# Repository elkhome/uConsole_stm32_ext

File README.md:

# uConsole_stm32_ext
STM32 extension card for uConsole.

Design is not finished and has not been tested.

Design based on dotcypress's uHub board, with identical USB port positioning: https://github.com/dotcypress/uhub

STM32 design learned from Sleepdealr's Kingsaver Replacement PCB: https://github.com/Sleepdealr/Kingsaver-Replacement-PCB

The goal is to get some of the functionality of both boards together, at a slightly lower manufacturing cost.

- Two USB C ports connected directly to the USB C pins, to avoid the need for a USB hub.
- STM32 replacing the RP2040, to avoid the need for crystal or flash components.
- Connecting the microcontroller to the uConsole via GPIO instead of USB, to both preserve uConsole’s USB lines and make the microcontroller’s USB lines externally accessible.
- Same USB C ports in the same position as the uHub, so the same faceplate should work for both.

With a CM4, you’d be able to program the STM32 over UART or I2C. With any other core, it will still work, but if they don’t have UART or I2C support for those pins, you might need to program the STM32 externally over USB.

The pins to program and reset the STM32 would be accessible either by physical button or over GPIO.

My main goal for the STM32 would be to use it as a USB HID device, sending keyboard commands to a headless computer over USB.

If I can find physical space on the board, I might also try to break out more microcontroller pins to possibly allow myself to solder in a sensor or LEDs or something.

Power management is dependent on the uConsole (there’s no on-board linear regulator, and the device USB port has it’s power line disconnected). In theory, I could change this?

This is my first STM32 project and my first fully assembled PCB project (I’ve only done keyboards before), so I’m not entirely sure what I’m doing.

https://forum.clockworkpi.com/t/stm32-ext-board-concept-thoughts/13368

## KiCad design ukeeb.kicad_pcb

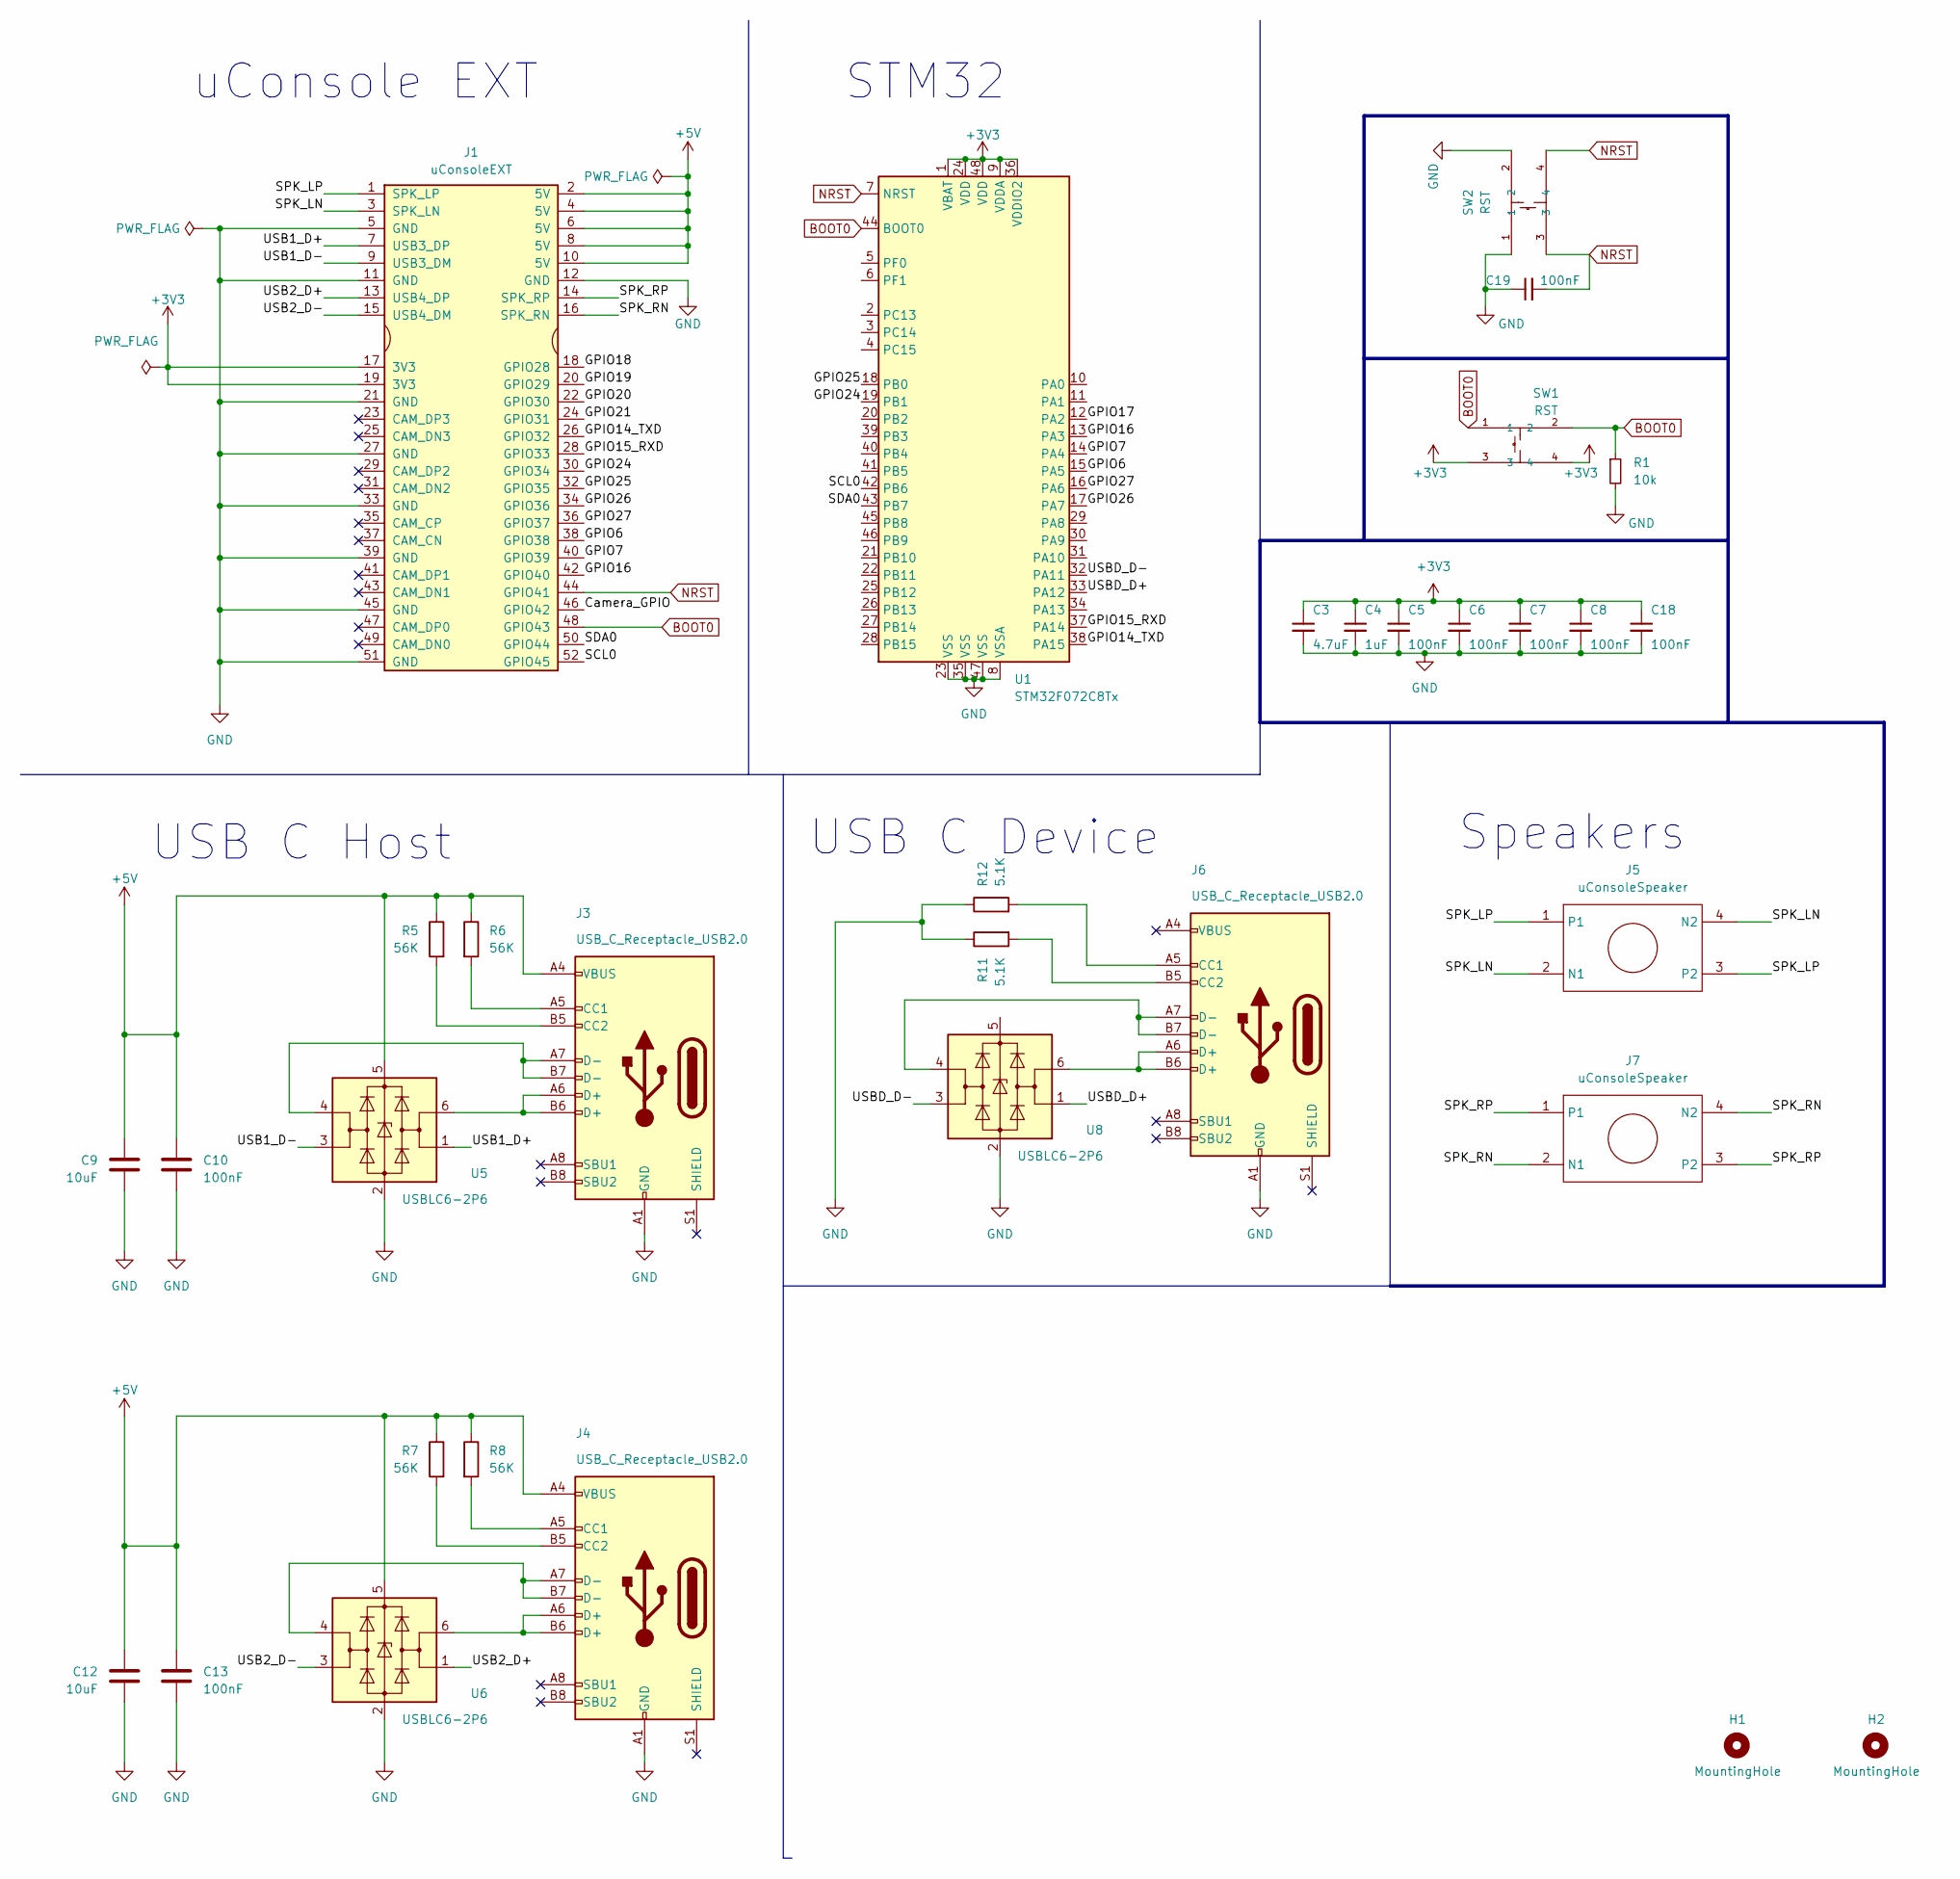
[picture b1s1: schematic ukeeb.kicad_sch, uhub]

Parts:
C3: 4.7uF; C_0402_1005Metric; LCSC C52923
C4: 1uF; C_0402_1005Metric; LCSC C52923
C5, C6, C7, C8, C18, C19: 100nF; C_0402_1005Metric; LCSC C307331
C9, C12: 10uF; C_0603_1608Metric
C10, C13: 100nF; C_0402_1005Metric
H1, H2: MountingHole; MountingHole_5.3mm_M5
J1: uConsoleEXT; ext
J3, J4, J6: USB_C_Receptacle_USB2.0; USB_C_Receptacle_HRO_TYPE-C-31-M-12
J5, J7: uConsoleSpeaker; speaker
R1: 10k; R_0402_1005Metric
R5, R6, R7, R8: 56K; R_0402_1005Metric
R11, R12: 5.1K; R_0402_1005Metric
SW1, SW2: RST; KEY-SMD_4P-L4.2-W3.2-P2.20-LS4.6; LCSC C139797
U1: STM32F072C8Tx; LQFP-48_7x7mm_P0.5mm
U5, U6, U8: USBLC6-2P6; SOT-666

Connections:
+3V3: C3.1, C4.1, C5.1, C6.1, C7.1, C8.1, C18.1, J1.17 (3V3), J1.19 (3V3), SW1.3, SW1.4, U1.1 (VBAT), U1.9 (VDDA), U1.24 (VDD), U1.36 (VDDIO2), U1.48 (VDD)
+5V: C9.2, C10.2, C12.2, C13.2, J1.2 (5V), J1.4 (5V), J1.6 (5V), J1.8 (5V), J1.10 (5V), J3.A4 (VBUS), J3.A9 (VBUS), J3.B4 (VBUS), J3.B9 (VBUS), J4.A4 (VBUS), J4.A9 (VBUS), J4.B4 (VBUS), J4.B9 (VBUS), R5.1, R6.1, R7.1, R8.1, U5.5 (VBUS), U6.5 (VBUS)
/Camera_GPIO: J1.46 (GPIO42)
/GPIO6: J1.38 (GPIO38), U1.15 (PA5)
/GPIO7: J1.40 (GPIO39), U1.14 (PA4)
/GPIO14_TXD: J1.26 (GPIO32), U1.38 (PA15)
/GPIO15_RXD: J1.28 (GPIO33), U1.37 (PA14)
/GPIO16: J1.42 (GPIO40), U1.13 (PA3)
/GPIO17: U1.12 (PA2)
/GPIO18: J1.18 (GPIO28)
/GPIO19: J1.20 (GPIO29)
/GPIO20: J1.22 (GPIO30)
/GPIO21: J1.24 (GPIO31)
/GPIO24: J1.30 (GPIO34), U1.19 (PB1)
/GPIO25: J1.32 (GPIO35), U1.18 (PB0)
/GPIO26: J1.34 (GPIO36), U1.17 (PA7)
/GPIO27: J1.36 (GPIO37), U1.16 (PA6)
/SCL0: J1.52 (GPIO45), U1.42 (PB6)
/SDA0: J1.50 (GPIO44), U1.43 (PB7)
/SPK_LN: J1.3 (SPK_LN), J5.2 (N1), J5.4 (N2)
/SPK_LP: J1.1 (SPK_LP), J5.1, J5.3 (P2)
/SPK_RN: J1.16 (SPK_RN), J7.2 (N1), J7.4 (N2)
/SPK_RP: J1.14 (SPK_RP), J7.1, J7.3 (P2)
/USB1_D+: J1.7 (USB3_DP), U5.1 (I/O1)
/USB1_D-: J1.9 (USB3_DM), U5.3 (I/O2)
/USB2_D+: J1.13 (USB4_DP), U6.1 (I/O1)
/USB2_D-: J1.15 (USB4_DM), U6.3 (I/O2)
/USBD_D+: U1.33 (PA12), U8.1 (I/O1)
/USBD_D-: U1.32 (PA11), U8.3 (I/O2)
BOOT0: J1.48 (GPIO43), R1.1, SW1.1, SW1.2, U1.44 (BOOT0)
GND: C3.2, C4.2, C5.2, C6.2, C7.2, C8.2, C9.1, C10.1, C12.1, C13.1, C18.2, C19.1, J1.5 (GND), J1.11 (GND), J1.12 (GND), J1.21 (GND), J1.27 (GND), J1.33 (GND), J1.39 (GND), J1.45 (GND), J1.51 (GND), J3.A1 (GND), J3.A12 (GND), J3.B1 (GND), J3.B12 (GND), J4.A1 (GND), J4.A12 (GND), J4.B1 (GND), J4.B12 (GND), J6.A1 (GND), J6.A12 (GND), J6.B1 (GND), J6.B12 (GND), R1.2, R11.1, R12.1, SW2.1, SW2.2, U1.8 (VSSA), U1.23 (VSS), U1.35 (VSS), U1.47 (VSS), U5.2 (GND), U6.2 (GND), U8.2 (GND)
NRST: C19.2, J1.44 (GPIO41), SW2.3, SW2.4, U1.7 (NRST)
unnamed: J3.A5 (CC1), R6.2
unnamed: J3.B5 (CC2), R5.2
unnamed: J3.A6 (D+), J3.B6 (D+), U5.6 (I/O1)
unnamed: J3.A7 (D-), J3.B7 (D-), U5.4 (I/O2)
unnamed: J4.A5 (CC1), R8.2
unnamed: J4.B5 (CC2), R7.2
unnamed: J4.A6 (D+), J4.B6 (D+), U6.6 (I/O1)
unnamed: J4.A7 (D-), J4.B7 (D-), U6.4 (I/O2)
unnamed: J6.A5 (CC1), R12.2
unnamed: J6.B5 (CC2), R11.2
unnamed: J6.A6 (D+), J6.B6 (D+), U8.6 (I/O1)
unnamed: J6.A7 (D-), J6.B7 (D-), U8.4 (I/O2)

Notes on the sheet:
uConsole EXT
STM32
Speakers
USB C Host
USB C Device

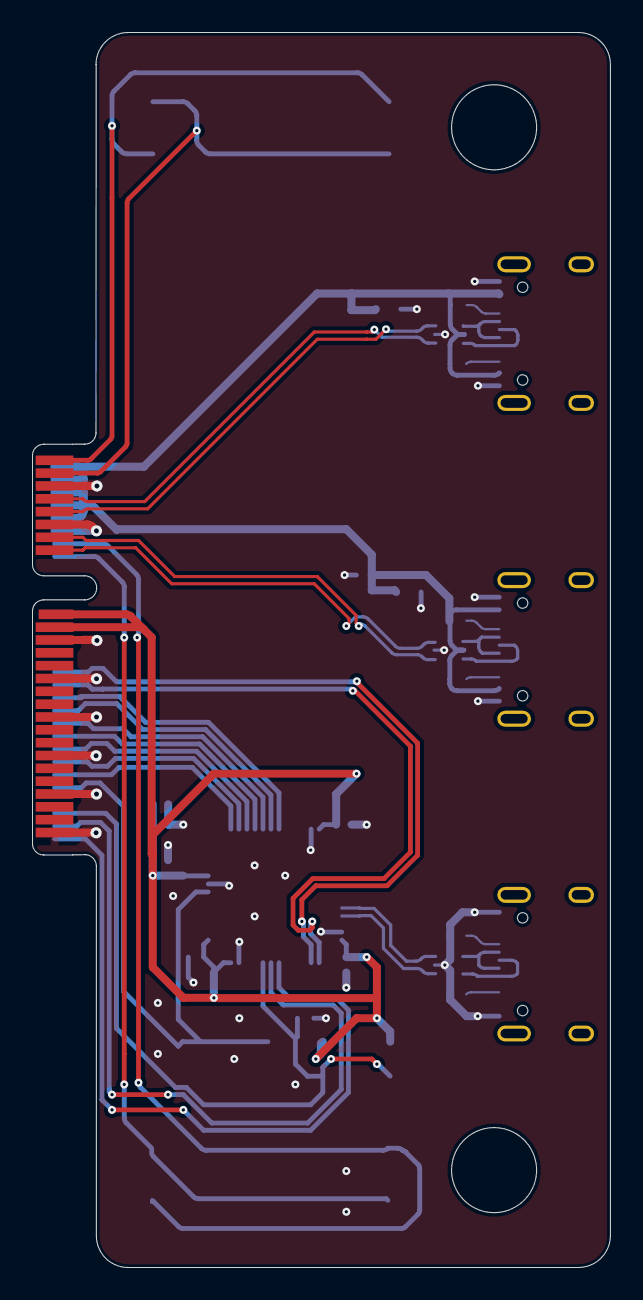
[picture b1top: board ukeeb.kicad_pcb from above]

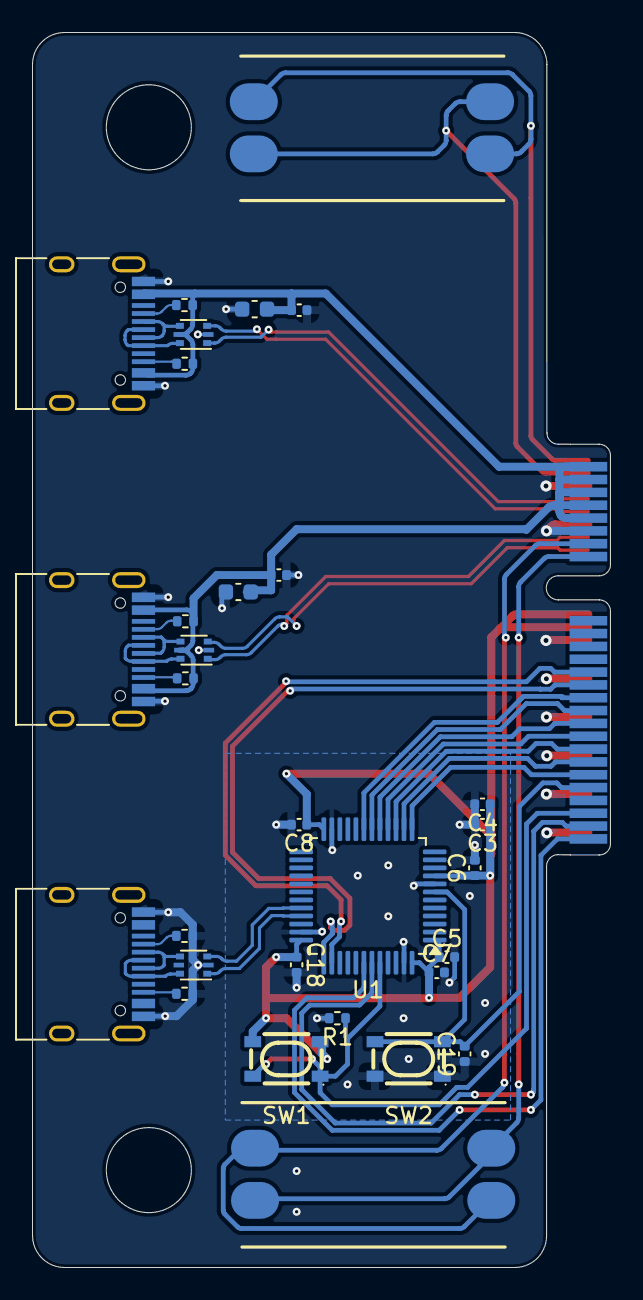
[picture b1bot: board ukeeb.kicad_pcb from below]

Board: 4 copper layers, 36.0 x 77.0 mm, 33 parts (30 on the bottom side), 38 nets.

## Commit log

2024-05-17 Initial project upload.
